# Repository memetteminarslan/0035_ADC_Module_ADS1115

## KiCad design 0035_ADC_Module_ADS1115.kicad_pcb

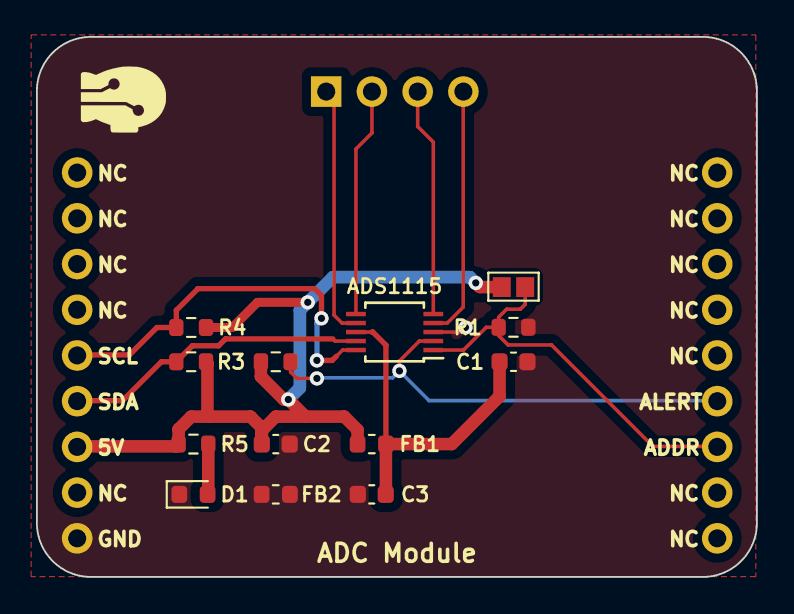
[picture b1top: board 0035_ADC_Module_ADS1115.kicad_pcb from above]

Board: 2 copper layers, 40.0 x 30.0 mm, 15 parts (0 on the bottom side), 12 nets.

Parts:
C1, C2: 10uF; C_0603_1608Metric
C3: 0.1uF; C_0603_1608Metric
D1: LED; LED_0603_1608Metric
FB1, FB2: FerriteBead; L_0603_1608Metric
J1: Conn_01x04_Socket; PinSocket_1x04_P2.54mm_Vertical
JP1: Jumper_2_Open; SolderJumper-2_P1.3mm_Open_Pad1.0x1.5mm
R1, R3, R4: 10K; R_0603_1608Metric
R2: 10k; R_0603_1608Metric
R5: 470r; R_0603_1608Metric
U1: ADS1115; TSSOP-10_3x3mm_P0.5mm
U3: pin_header

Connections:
+5V: C2.1, FB1.1, JP1.2 (B), R2.1, R3.1, R4.1, R5.1, U3.7
ADDR: JP1.1 (A), R1.1, U1.1 (ADDR), U3.12
AIN0: J1.4, U1.4 (AIN0)
AIN1: J1.3, U1.5 (AIN1)
AIN2: J1.2, U1.6 (AIN2)
AIN3: J1.1, U1.7 (AIN3)
ALERT: R2.2, U1.2 (ALERT/RDY), U3.13
GND: C1.2, C2.2, C3.2, D1.1 (K), FB2.1, FB2.2, R1.2, U1.3 (GND), U3.9
unnamed: D1.2 (A), R5.2
SCL: R4.2, U1.10 (SCL), U3.5
SDA: R3.2, U1.9 (SDA), U3.6
VCC: C1.1, C3.1, FB1.2, U1.8 (VDD)
